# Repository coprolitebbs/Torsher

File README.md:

# Torsher

Плата и прошивка домашнего торшера.

Данный торшер существует в единственном экземпляре, сварен из маховика, рулевой рейки от Террано в 50 кузове, манометра от УАЗа, и вам он не нужен, поверьте. Разве что сгодится за хорошее орудие самообороны.

При старте контроллера первый раз (при пустом сохраненном имени WiFi-точки доступа в настройках), контроллер заводит свою точку доступа с именем Torsher.
Подключившись к ней (в браузере по адресу 192.168.1.2 либо при подключении к точке автоматически выпадет Captive-форма), можно настроить параметры для работы в сети WiFi:

WIFI - Имя точки, к которой подключаться
Password - Пароль
Local IP - Локальный статический адрес. Нужен для работы с торшером из сети.

Освещение - Параметры, срабатывающие при включенном среднем выключателе торшера (Автоматический режим)

От .. до 24 - Доп. подсветка - Включающийся автоматически вечером люминесцентный шнур.
Утр. работа и Веч. работа - часы, задающие автоматическое включение основной лампы.

Установленное время - позволяет настроить текущее время часов контроллера.

При настроенных параметрах торшер при рестарте будет подключаться к сети автоматически при подаче питания.
Цикл подключения длится примерно полторы минуты. Если к настроенной сети подключение не удастся, торшер кратко три раза мигнет дополнительной подсветкой ит запустит собственную точку доступа.
Если же подключение к сети удалось, торшер количеством миганий дополнительной подсветки отсчитает текущий час.

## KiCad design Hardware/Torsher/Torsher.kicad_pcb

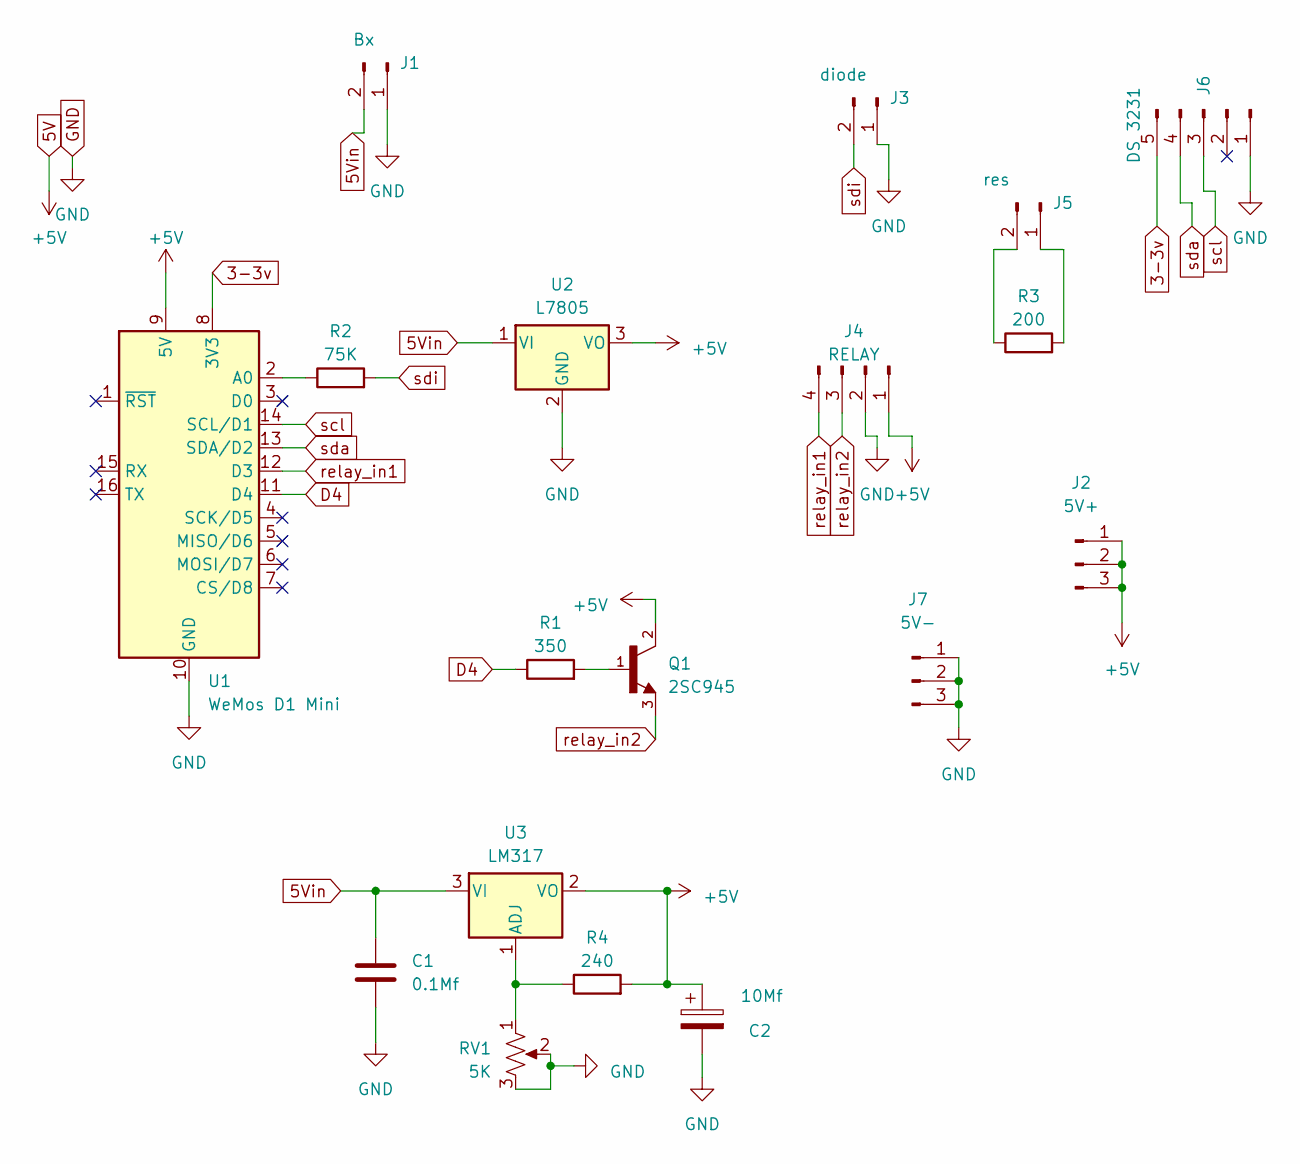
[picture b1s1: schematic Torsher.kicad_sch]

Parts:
C1: 0.1Mf; C_Axial_L3.8mm_D2.6mm_P7.50mm_Horizontal
C2: 10Mf; CP_Radial_D5.0mm_P2.50mm
J1: Bx; PinSocket_1x02_P2.54mm_Vertical
J2: 5V+; PinSocket_1x03_P2.54mm_Vertical
J3: diode; PinSocket_1x02_P2.54mm_Vertical
J4: RELAY; PinSocket_1x04_P2.54mm_Vertical
J5: res; PinSocket_1x02_P2.54mm_Vertical
J6: DS 3231; PinSocket_1x05_P2.54mm_Vertical
J7: 5V-; PinSocket_1x03_P2.54mm_Vertical
Q1: 2SC945; TO92
R1: 350; R_Axial_DIN0207_L6.3mm_D2.5mm_P15.24mm_Horizontal
R2: 75K; R_Axial_DIN0207_L6.3mm_D2.5mm_P15.24mm_Horizontal
R3: 200; R_Axial_DIN0207_L6.3mm_D2.5mm_P15.24mm_Horizontal
R4: 240; R_Axial_DIN0207_L6.3mm_D2.5mm_P15.24mm_Horizontal
RV1: 5K; Potentiometer_Bourns_3296W_Vertical
U1: WeMos D1 Mini; WEMOS_D1_mini_light
U2: L7805; TO-220-3_Vertical
U3: LM317; TO-220-3_Vertical

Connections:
3-3v: J6.5, U1.8 (3V3)
5V: C2.1, J2.1, J2.2, J2.3, J4.1, Q1.2, R4.2, U1.9 (5V), U2.3 (VO), U3.2 (VO)
5Vin: C1.2, J1.2, U2.1 (VI), U3.3 (VI)
D4: R1.1, U1.11 (D4)
GND: C1.1, C2.2, J1.1, J3.1, J4.2, J6.1, J7.1, J7.2, J7.3, RV1.2, RV1.3, U1.10 (GND), U2.2 (GND)
unnamed: J5.1, R3.2
unnamed: J5.2, R3.1
unnamed: Q1.1, R1.2
unnamed: R2.1, U1.2 (A0)
unnamed: R4.1, RV1.1, U3.1 (ADJ)
relay_in1: J4.4, U1.12 (D3)
relay_in2: J4.3, Q1.3
scl: J6.3, U1.14 (SCL/D1)
sda: J6.4, U1.13 (SDA/D2)
sdi: J3.2, R2.2

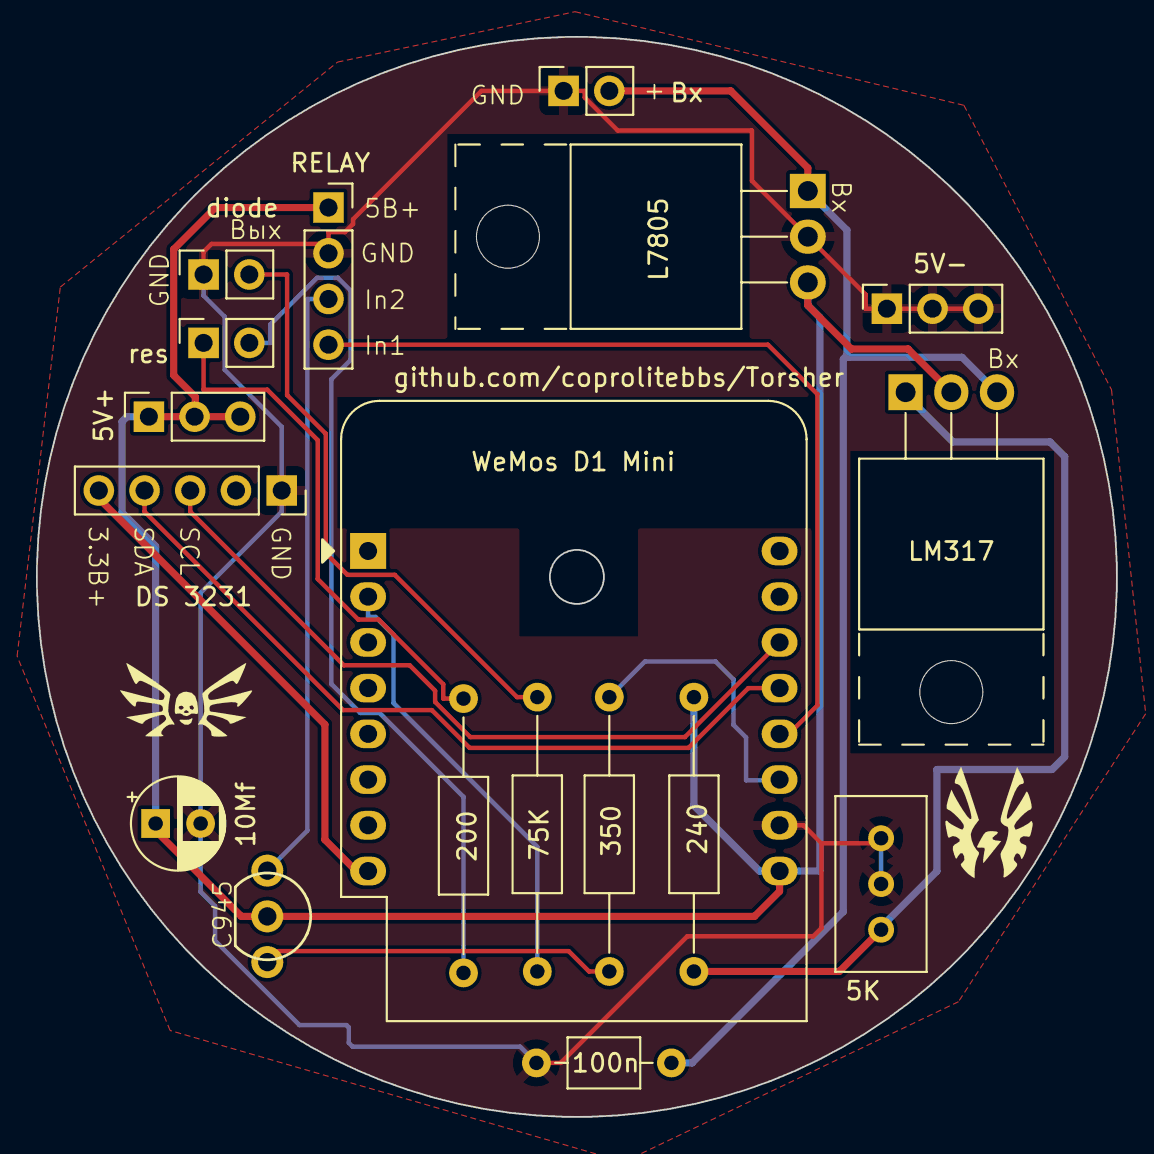
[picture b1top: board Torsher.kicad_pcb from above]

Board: 2 copper layers, 60.0 x 60.0 mm, 20 parts (0 on the bottom side), 15 nets.

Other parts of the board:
Strogg engineer logo: LOGO
Strogg logo: LOGO

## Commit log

2023-12-31 Add files via upload
    little fix
